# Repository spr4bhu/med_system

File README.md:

# Dual-ESP32 Medical Monitoring System

## Overview

A secure IoT medical monitoring and access control system using two ESP32 microcontrollers with ESP-IDF framework. Real-time vital monitoring with fall detection, posture recognition, and RFID-based access control.

### Architecture

```
┌──────────────────────────────────────────────────────────┐
│           HiveMQ Cloud MQTT Broker (TLS)                 │
│              mqtts://*.eu.hivemq.cloud:8883              │
└────────────────────────▲─────────────────────────────────┘
                         │ MQTT over TLS
                         │
         ┌───────────────┴──────────────┐
         │                              │
    ┌────▼──────────────┐      ┌───────▼─────────┐
    │    Node A         │      │    Node B       │
    │  (Vital Monitor)  │      │   (Sentry)      │
    │                   │      │                 │
    │ - MPU6050 (Fall)  │      │ - RC522 RFID    │
    │ - DHT11 (Temp)    │      │ - IR Motion     │
    │ - HW-827 (Heart)  │      │ - Buzzer Alarm  │
    │ - Button (SOS)    │      │                 │
    └──────────┬────────┘      └────────┬────────┘
               │ ESP-NOW P2P           │
               └───────────────────────┘
                  (Emergency alerts)
```

## Hardware Requirements

### Node A: Vital Monitor (Medical Monitoring)
- **Microcontroller**: ESP32 DevKit V1
- **Sensors**:
  - MPU6050 (I2C: GPIO 21/22) - 6-axis IMU for fall detection + posture
  - DHT11 (GPIO 5) - Temperature & humidity (1-wire protocol)
  - HW-827 (GPIO 36, ADC) - Heart rate sensor
  - Emergency Button (GPIO 4, active LOW) - Manual SOS trigger

### Node B: Sentry (Access Control & Security)
- **Microcontroller**: ESP32 DevKit V1
- **Sensors**:
  - RC522 RFID Reader (SPI: GPIO 23/25/19/22) - Access control
  - IR Motion Sensor (GPIO 13) - Intrusion detection
  - Buzzer (GPIO 5, NPN driver) - Alarm output

### Common Requirements
- 3.3V power via AMS1117 regulator
- USB-C or Li-ion battery (3.7-4.2V)
- Breadboards and jumper wires
- Git and ESP-IDF 5.1+

## Software Requirements

- **ESP-IDF v5.1+** - [Installation Guide](https://docs.espressif.com/projects/esp-idf/en/latest/esp32/get-started/)
- **Git** - For version control
- **HiveMQ Cloud Account** - Free tier MQTT broker

## Quick Start

### 1. Setup ESP-IDF

```bash
mkdir -p ~/esp
cd ~/esp
git clone --recursive https://github.com/espressif/esp-idf.git
cd esp-idf
./install.sh esp32
source export.sh
```

### 2. Clone Repository

```bash
cd ~
git clone https://github.com/vruga/esp_medmonitor.git
cd esp_medmonitor
git checkout shashvatt
```

### 3. Configure Credentials

```bash
cp node-a-gateway/main/config.h.template node-a-gateway/main/config.h
cp node-b-sentry/main/config.h.template node-b-sentry/main/config.h

# Edit with your WiFi and HiveMQ credentials
nano node-a-gateway/main/config.h
nano node-b-sentry/main/config.h
```

### 4. Build and Flash Node A

```bash
cd node-a-gateway
idf.py build
idf.py -p /dev/cu.usbserial-XXXXX flash monitor
```

### 5. Build and Flash Node B

```bash
cd ../node-b-sentry
idf.py build
idf.py -p /dev/cu.usbserial-YYYYY flash monitor
```

## Pin Configuration

### Node A GPIO Mapping
| Component | GPIO | Protocol | Purpose |
|-----------|------|----------|---------|
| MPU6050 SDA | 21 | I2C | Accelerometer/Gyroscope data |
| MPU6050 SCL | 22 | I2C | Accelerometer/Gyroscope clock |
| DHT11 Data | 5 | 1-Wire | Temperature & humidity |
| HW-827 ADC | 36 | ADC1_CH0 | Heart rate sensor |
| Emergency Button | 4 | GPIO Input | SOS button (active LOW) |
| UART TX | 1 | UART | Serial output (115200 baud) |
| UART RX | 3 | UART | Serial input |

### Node B GPIO Mapping
| Component | GPIO | Protocol | Purpose |
|-----------|------|----------|---------|
| RC522 MOSI | 23 | SPI | RFID data in |
| RC522 MISO | 25 | SPI | RFID data out |
| RC522 SCLK | 19 | SPI | RFID clock |
| RC522 CS | 22 | SPI | RFID chip select |
| IR Sensor | 13 | GPIO Input | Motion detection |
| Buzzer | 5 | GPIO Output | Alarm (NPN driver) |
| UART TX | 1 | UART | Serial output |
| UART RX | 3 | UART | Serial input |

## Features

### Node A: Vital Monitoring
- ✅ **Fall Detection**: Jerk-based algorithm (200 g/s threshold) with 2s cooldown
- ✅ **Posture Recognition**: Complementary filter (99% gyro + 1% accel)
  - STANDING: pitch ≤ 15°
  - SITTING: pitch ≥ 20°
  - LYING: pitch & roll ≤ 10°
- ✅ **Heart Rate Monitoring**: Peak detection on HW-827 sensor
- ✅ **Temperature Tracking**: DHT11 with retry logic (WiFi interference tolerance)
- ✅ **Emergency Button**: Manual SOS trigger
- ✅ **MQTT Publishing**: Real-time sensor data to HiveMQ Cloud
- ✅ **ESP-NOW**: Emergency messages to Node B (dynamic channel)

### Node B: Access Control & Security
- ✅ **RFID Access Control**: RC522 reader with full SPI protocol
  - Request → Anticollision → UID database lookup
  - Authorized/Unauthorized card detection
- ✅ **IR Motion Detection**: PIR sensor with state machine
- ✅ **Security State Machine**: IDLE → IR_DETECTED → AUTHORIZED/INTRUSION
- ✅ **Buzzer Alarm**: GPIO-driven NPN transistor
- ✅ **MQTT Publishing**: Security events to HiveMQ Cloud
- ✅ **ESP-NOW Receiver**: Listens for emergencies from Node A

### Network & Communication
- ✅ **WiFi**: STA mode with auto-reconnect
- ✅ **MQTT over TLS**: HiveMQ Cloud with certificate verification
- ✅ **SNTP**: Time synchronization via pool.ntp.org
- ✅ **ESP-NOW**: Dynamic channel detection (follows WiFi AP channel)
- ✅ **DHT11 Retry**: Up to 3 retries on checksum errors

## MISRA-C Compliance

Code follows MISRA-C:2012 guidelines:
- ✅ Rule 8.4: Function prototypes in headers
- ✅ Rule 14.4: All if-else chains have final else
- ✅ Rule 17.7: All return values checked
- ✅ Rule 10.3/10.4: Explicit type casts
- ✅ Rule 2.7: Unused parameters marked `(void)param`
- ✅ Rule 9.1: Variables initialized before use
- ✅ Compiles with `-Wall -Wextra -Werror`

## Testing

### Quick Test Setup
```bash
# Terminal 1: Node A
cd node-a-gateway && idf.py -p /dev/cu.usbserial-A monitor

# Terminal 2: Node B
cd node-b-sentry && idf.py -p /dev/cu.usbserial-B monitor
```

### Test Cases
1. **Fall Detection**: Shake/drop Node A → Watch for "FALL DETECTED"
2. **Posture**: Rotate Node A → Verify posture changes (STANDING/SITTING/LYING)
3. **Heart Rate**: Simulate sensor pulses → Peak count increases
4. **RFID Authorized**: Scan authorized card → Buzzer silent
5. **RFID Unauthorized**: Scan unknown card → Buzzer sounds
6. **Emergency**: Press button on Node A → Node B buzzer sounds
7. **MQTT**: Check HiveMQ console for all messages

## Troubleshooting

### ESP32 won't flash
```bash
ls /dev/cu.usbserial-*
# Hold BOOT button while connecting
```

### DHT11 timeouts
- External 2.2kΩ pull-up required on GPIO 5
- Keep wire short (<10cm)
- Check 3.3V power

### ESP-NOW not working
- Both nodes must be on same WiFi channel
- Verify MAC addresses match actual hardware
- Both must be powered on WiFi

### MQTT connection fails
- Check WiFi SSID/password in config.h
- Verify HiveMQ credentials
- Ensure TLS certificate is correct

### RFID not detected
- Check SPI wiring (MOSI/MISO/SCLK)
- Verify RC522 at 3.3V (not 5V)
- Try increasing SPI clock if needed

## Build Options

```bash
idf.py fullclean && idf.py build
idf.py -v build                    # Verbose output
idf.py build -j8                   # Parallel build
idf.py menuconfig                  # Configuration
idf.py monitor --timestamp         # Monitor with timestamps
```

## Project Structure

```
esp_medmonitor/
├── node-a-gateway/          # Vital Monitor firmware
│   ├── main/
│   │   ├── config.h.template
│   │   ├── sensors/         # MPU6050, DHT11, HW-827
│   │   ├── tasks/           # Fall detection, sensor, MQTT
│   │   └── utils/
│   └── CMakeLists.txt
├── node-b-sentry/           # Access Control firmware
│   ├── main/
│   │   ├── config.h.template
│   │   ├── modules/         # RFID, IR, Buzzer
│   │   ├── tasks/           # Security, MQTT
│   │   └── utils/
│   └── CMakeLists.txt
├── Hackthon_PCB/            # KiCAD schematics & layouts
│   ├── Hackthon_PCB.kicad_sch
│   ├── Hackthon_PCB.kicad_pcb
│   ├── gerbers/
│   └── kicad_parts/
└── README.md
```

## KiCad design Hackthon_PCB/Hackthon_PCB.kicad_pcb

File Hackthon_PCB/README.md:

# Medical Monitoring System - PCB Design

KiCAD project for dual-node ESP32 medical monitoring and security system.

## Files

### Design Files
- **Hackthon_PCB.kicad_pro** - Project configuration
- **Hackthon_PCB.kicad_sch** - Schematic (both Node A & B)
- **Hackthon_PCB.kicad_pcb** - PCB layout

### Libraries
- **kicad_parts/** - Custom footprints and symbols (Charleslabs_Parts)
- **MY_lib.kicad_sym** - Additional custom symbols
- **sym-lib-table** - Symbol library configuration

### Manufacturing
- **gerbers/** - Gerber files for PCB fabrication
  - Copper layers (F_Cu, B_Cu)
  - Silkscreen layers
  - Solder mask layers
  - Drill files (PTH, NPTH)
  - Job file for fab house

## Design Notes

### Node A: Vital Detector (Medical Monitoring)

**Sensors:**
- MPU6050 (I2C: GPIO 21/22) - Fall detection + posture
- DHT11 (1-wire: GPIO 5) - Temperature & humidity
- HW-827 (ADC: GPIO 36) - Heart rate
- Emergency Button (GPIO 4) - Manual SOS trigger

**Schematic:**

**PCB Layout:**

---

### Node B: Authenticator (Security Monitoring)

**Sensors:**
- RC522 RFID (SPI: GPIO 23/25/19/22) - Access control
- IR Motion Sensor (GPIO 13) - Intrusion detection
- Buzzer (GPIO 5, NPN driver) - Alarm output

**Schematic:**

**PCB Layout:**

---

### Power Supply

- **Regulator:** AMS1117-3.3 (500mA)
- **Input:** USB-C 5V or Li-ion battery (3.7-4.2V)
- **Output:** 3.3V for ESP32 and peripherals
- **Decoupling:** 10µF bulk + 100nF per IC
- **Protection:** Reverse polarity diode, USB overvoltage

## Usage

1. Open `Hackthon_PCB.kicad_pro` in KiCAD 8.x+
2. Schematic: `Hackthon_PCB.kicad_sch`
3. Layout: `Hackthon_PCB.kicad_pcb`
4. Export gerbers from PCB layout for manufacturing

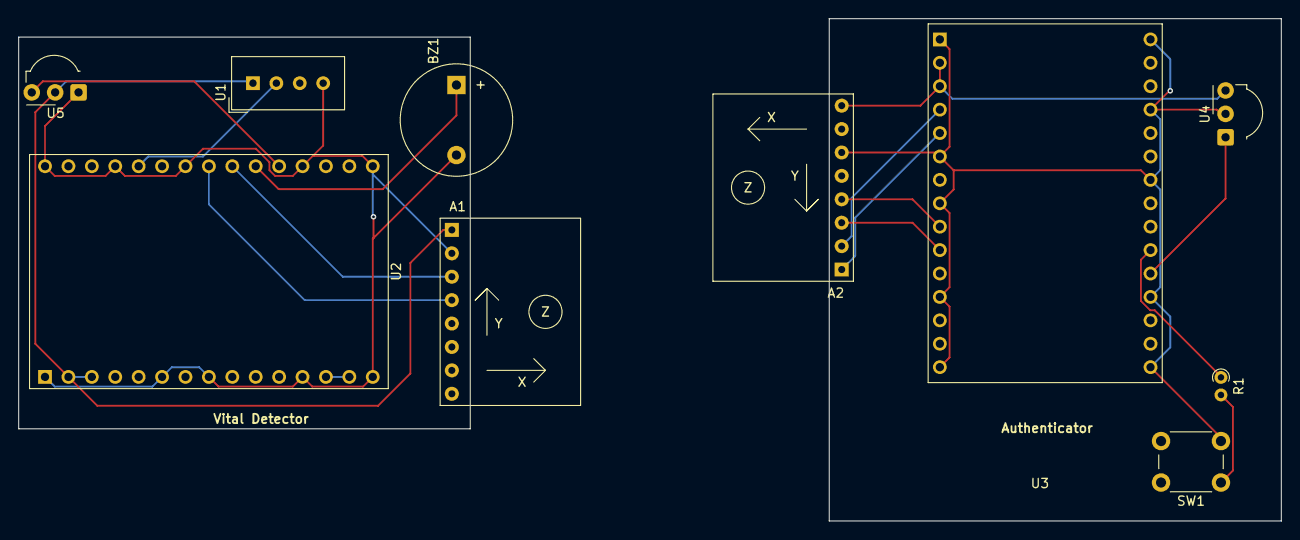
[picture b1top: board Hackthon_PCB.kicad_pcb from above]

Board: 2 copper layers, 137.0 x 54.5 mm, 10 parts (0 on the bottom side), 18 nets.

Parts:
A1: MPU6050_Module
A2: rfid-rc522; MPU6050_Module
BZ1: Buzzer; Buzzer_12x9.5RM7.6
R1: R; R_Axial_DIN0204_L3.6mm_D1.6mm_P1.90mm_Vertical
SW1: SW_Push; SW_PUSH_6mm
U1: DHT11; Aosong_DHT11_5.5x12.0_P2.54mm
U2, U3: ESP32-C3-DevKitM-1
U4: IR; Vishay_MOLD-3Pin
U5: hw827 Heartrate; Vishay_MOLD-3Pin

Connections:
unnamed: A1.2 (GND), BZ1.2 (-), U1.4 (GND), U2.1 (GND), U2.6 (GND), U2.8 (GND), U2.12 (GND), U2.15 (GND), U2.16 (GND), U2.19 (GND), U2.24 (GND), U2.27 (GND), U2.30 (GND), U5.1 (GND)
unnamed: A1.3 (SCL), U2.22 (IO6)
unnamed: A1.4 (SDA), U2.23 (IO7)
unnamed: A1.1 (VCC), U1.1 (VDD), U2.2 (3V3), U2.3 (3V3), U5.2 (Vs)
unnamed: A2.8 (3.3V), U3.2 (3V3), U3.3 (3V3), U4.3 (Vs)
unnamed: A2.6 (GND), SW1.2, U3.1 (GND), U3.6 (GND), U3.8 (GND), U3.12 (GND), U3.15 (GND), U3.16 (GND), U3.19 (GND), U3.24 (GND), U3.27 (GND), U3.30 (GND), U4.2 (GND)
unnamed: A2.4 (MISO), U3.9 (IO0)
unnamed: A2.3 (MOSI), U3.10 (IO1)
unnamed: A2.2 (SCK), U3.4 (IO2)
unnamed: A2.1 (SDA), U3.5 (IO3)
unnamed: BZ1.1 (+), U2.21 (IO5)
unnamed: R1.2, SW1.1
unnamed: U1.2 (DATA), U2.26 (IO9)
unnamed: U2.13 (5V), U2.14 (5V)
unnamed: U2.20 (IO4), U5.3 (OUT)
unnamed: U3.13 (5V), U3.14 (5V)
unnamed: U3.20 (IO4), U4.1 (OUT)
unnamed: R1.1, U3.21 (IO5)

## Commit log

2026-02-07 Implement dual-ESP32 medical monitoring system firmware
2026-02-07 updated sensor
2026-02-07 missing dependencies
2026-02-08 it works
2026-02-08 dashboard file
2026-02-08 Add ML dashboard, RFID server and documentation from server branch
    - Dashboard with browser-based ML analytics (anomaly detection, predictions)
    - RFID logging server with REST API
    - Complete documentation guides
    - Updated .gitignore for cleaner repo
2026-02-08 readme update
2026-02-08 Fix README: correct pins, features, and architecture
2026-02-17 updating config and adding source files
